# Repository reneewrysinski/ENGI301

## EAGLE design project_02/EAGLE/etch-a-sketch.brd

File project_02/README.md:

This folder contains documentation, EAGLE files, and manufacturing files for my EDES301 PCB design project. This design is a PocketBeagle-based Etch-A-Sketch controlled by two potentiometers and two buttons with a 2.8" TFT screen to display the image being produced.

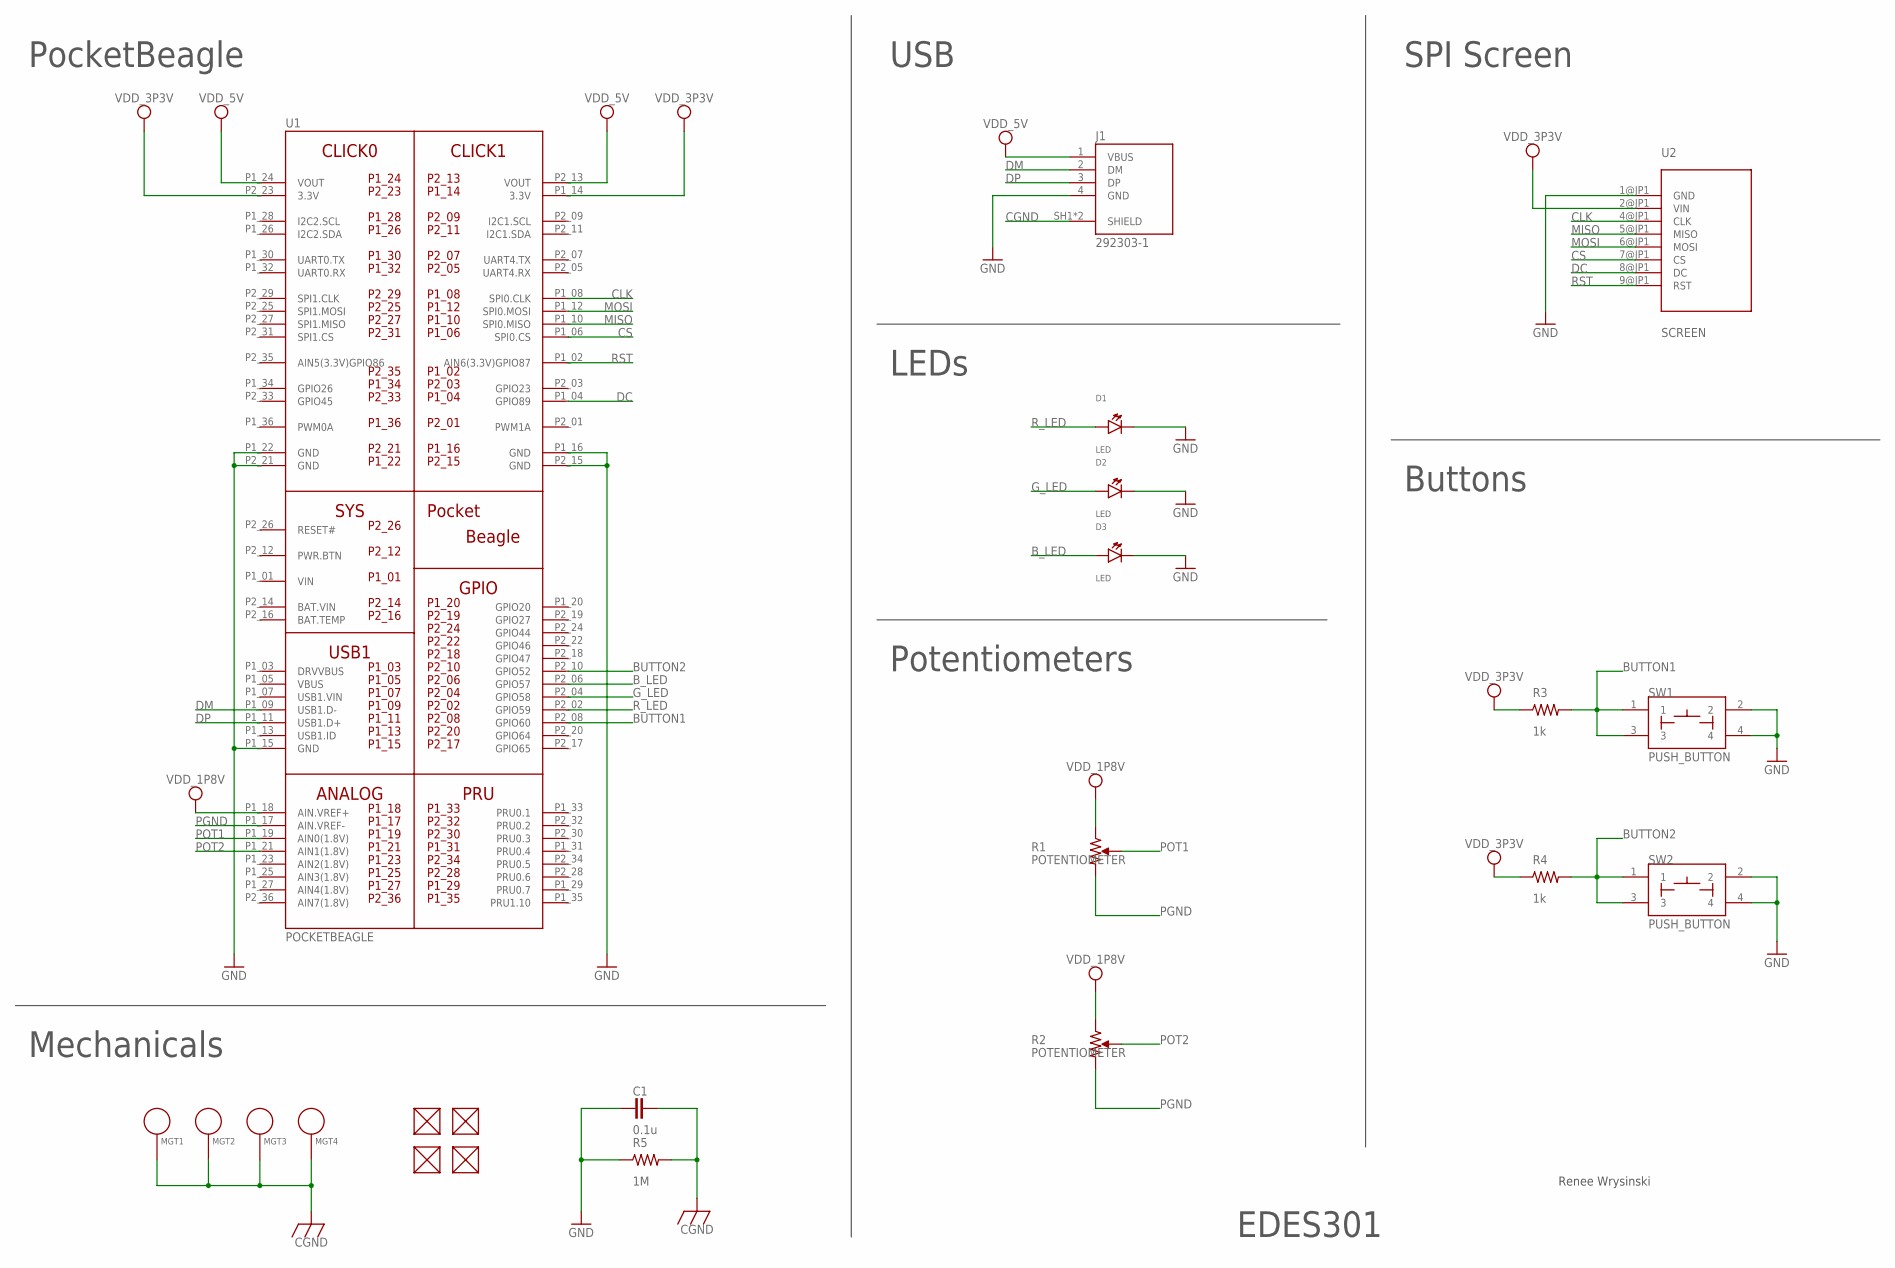
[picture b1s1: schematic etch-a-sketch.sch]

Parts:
C1: 0.1u; C0603
D1, D2, D3: LED; EIA-STD
FUD1, FUD2, FUD3, FUD4: FIDUCIAL; FIDUCIAL_40MIL
J1: 292303-1; TE_292303-1
MGT1, MGT2, MGT3, MGT4: MOUNTING_HOLE
R1, R2: POTENTIOMETER; POT-PO90S
R3, R4: 1k; R0603
R5: 1M; R0603
SW1, SW2: PUSH_BUTTON; BUTTON_12.5MM
U1: POCKETBEAGLE
U2: SCREEN; ADAFRUIT_2.8_TFT_BREAKOUT_V2

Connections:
BAT.VIN: U1.P2_14 (BAT.VIN)
BUTTON1: R3.2, SW1.1, SW1.3, U1.P2_08 (GPIO60)
BUTTON2: R4.2, SW2.1, SW2.3, U1.P2_10 (GPIO52)
B_LED: D3.ANODE, U1.P2_06 (GPIO57)
CGND: C1.2, J1.SH1 (SHIELD), J1.SH2 (SHIELD), MGT1.P$1, MGT2.P$1, MGT3.P$1, MGT4.P$1, R5.2
CLK: U1.P1_08 (SPI0.CLK), U2.4@JP1 (CLK)
CS: U1.P1_06 (SPI0.CS), U2.7@JP1 (CS)
DC: U1.P1_04 (GPIO89), U2.8@JP1 (DC)
DM: J1.2 (DM), U1.P1_09 (USB1.D-)
DP: J1.3 (DP), U1.P1_11 (USB1.D+)
GND: C1.1, D1.CATHODE, D2.CATHODE, D3.CATHODE, J1.4 (GND), R5.1, SW1.2, SW1.4, SW2.2, SW2.4, U1.P1_15 (GND), U1.P1_16 (GND), U1.P1_22 (GND), U1.P2_15 (GND), U1.P2_21 (GND), U2.1@JP1 (GND)
G_LED: D2.ANODE, U1.P2_04 (GPIO58)
MISO: U1.P1_10 (SPI0.MISO), U2.5@JP1 (MISO)
MOSI: U1.P1_12 (SPI0.MOSI), U2.6@JP1 (MOSI)
PGND: R1.CW, R2.CW, U1.P1_17 (AIN.VREF-)
POT1: R1.S, U1.P1_19 (AIN0(1.8V))
POT2: R2.S, U1.P1_21 (AIN1(1.8V))
RST: U1.P1_02 (AIN6(3.3V)GPIO87), U2.9@JP1 (RST)
R_LED: D1.ANODE, U1.P2_02 (GPIO59)
VDD_1P8V: R1.CCW, R2.CCW, U1.P1_18 (AIN.VREF+)
VDD_3P3V: R3.1, R4.1, U1.P1_14 (3.3V), U1.P2_23 (3.3V), U2.2@JP1 (VIN)
VDD_5V: J1.1 (VBUS), U1.P1_24 (VOUT), U1.P2_13 (VOUT)
VIN: U1.P1_01 (VIN)

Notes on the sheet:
PocketBeagle
Mechanicals
USB
LEDs
Potentiometers
Buttons
SPI Screen
EDES301
Renee Wrysinski

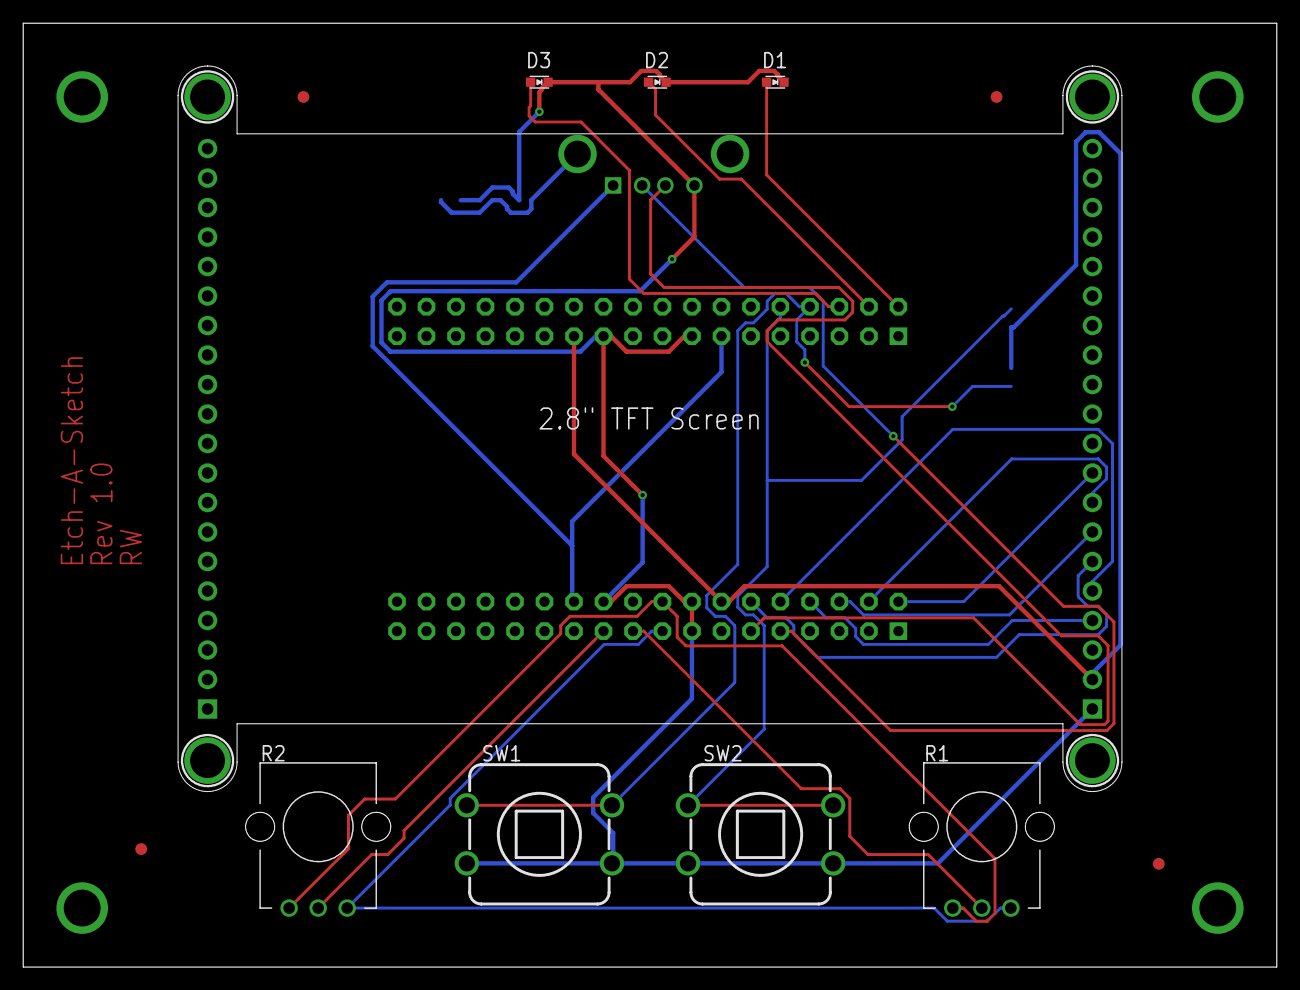
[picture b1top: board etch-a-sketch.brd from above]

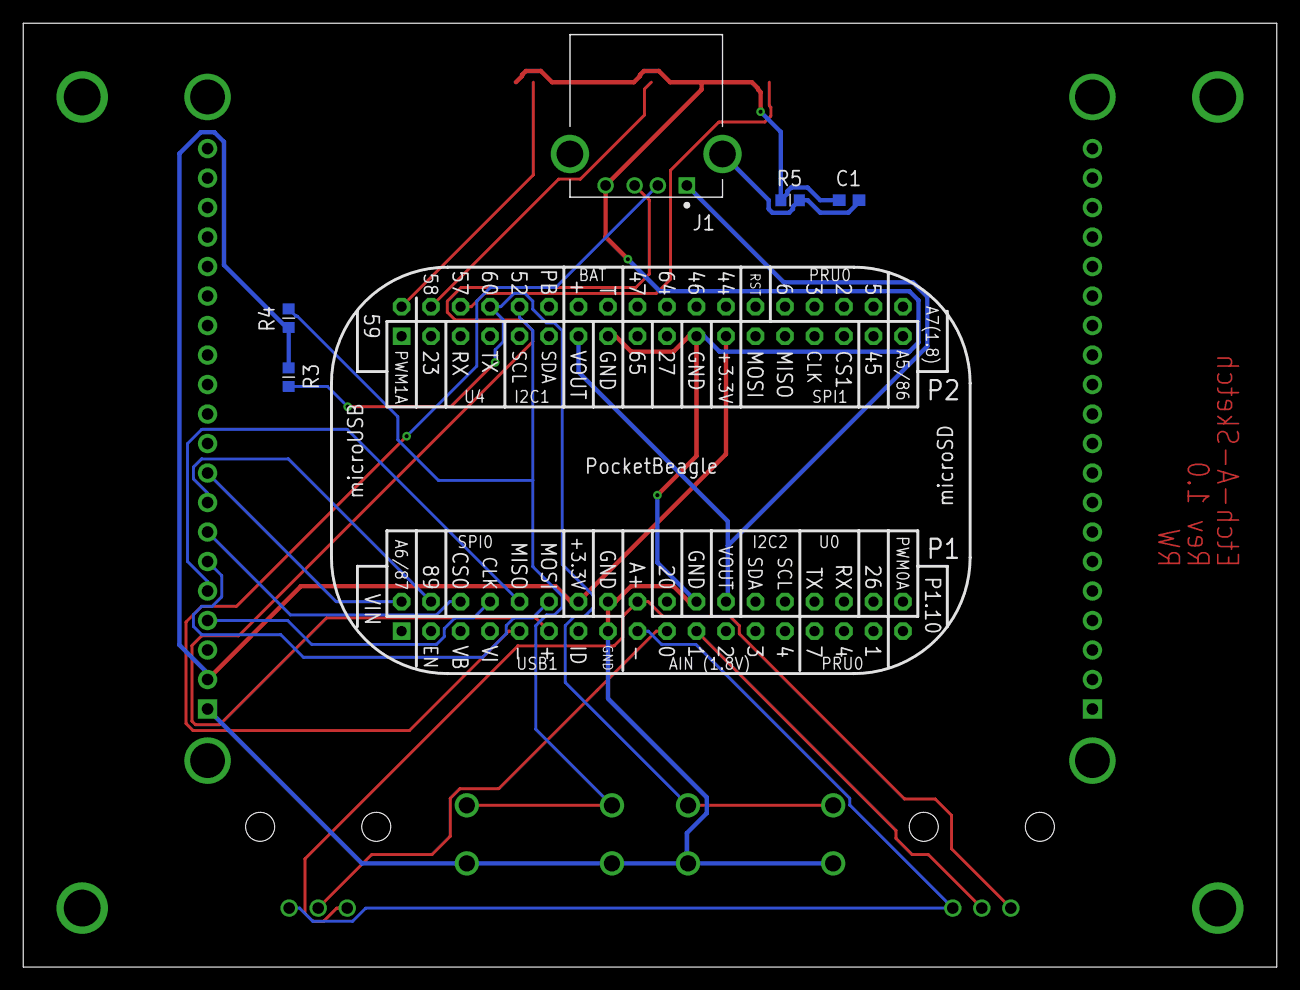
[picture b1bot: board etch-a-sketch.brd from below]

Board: 2 copper layers, 108.0 x 81.3 mm, 22 parts (6 on the bottom side), 21 nets.

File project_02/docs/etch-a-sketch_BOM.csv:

"Qty";"Value";"Device";"Package";"Parts";"Description";"AVAILABILITY";"CENTERLINE_PITCH";"COMMENT";"DESCRIPTION";"EU_ROHS_COMPLIANCE";"MF";"MP";"NUMBER_OF_POSITIONS";"PACKAGE";"PRICE";"PRODUCT_TYPE";"PURCHASE-URL";
"1";"0.1u";"C_C0603";"C0603";"C1";"Capacitor SMD.";"";"";"";"";"";"";"";"";"";"";"";"";
"1";"1M";"R_R0603";"R0603";"R5";"RESISTOR, American symbol";"";"";"";"";"";"";"";"";"";"";"";"";
"2";"1k";"R_R0603";"R0603";"R3, R4";"RESISTOR, American symbol";"";"";"";"";"";"";"";"";"";"";"";"";
"1";"292303-1";"292303-1";"TE_292303-1";"J1";"CONN USB RECEPT R/A TYPE A 4POS Check availability";"In Stock";"2 mm[.078 in]";"292303-1";" Conn";" Data";" USB";" Recept";" 2.0";" 4 Pos";" 1 Port";" Rt Angle";" A Ser";
"4";"FIDUCIAL";"FIDUCIAL";"FIDUCIAL_40MIL";"FUD1, FUD2, FUD3, FUD4";"";"";"";"";"";"";"";"";"";"";"";"";"";
"3";"LED";"LED";"EIA-STD";"D1, D2, D3";"EIA-STD LED, LTST-C191TBKT";"";"";"";"";"";"";"";"";"";"";"";"";
"4";"MOUNTING_HOLE";"MOUNTING_HOLE";"MOUNTING_HOLE";"MGT1, MGT2, MGT3, MGT4";"Chassis Mounting Hole w/GND connection ability";"";"";"";"";"";"";"";"";"";"";"";"";
"1";"POCKETBEAGLE";"POCKETBEAGLE";"POCKETBEAGLE";"U1";"";"";"";"";"";"";"";"";"";"";"";"";"";
"2";"POTENTIOMETER";"POTENTIOMETER";"POT-PO90S";"R1, R2";"Potentiometer - Examples:";"";"";"";"";"";"";"";"";"";"";"";"";
"2";"PUSH_BUTTON";"PUSH_BUTTON";"BUTTON_12.5MM";"SW1, SW2";"";"";"";"";"";"";"";"";"";"";"";"";"";
"1";"SCREEN";"ADAFRUIT_2.8_TFT_BREAKOUT_V2";"ADAFRUIT_2.8_TFT_BREAKOUT_V2";"U2";"";"";"";"";"";"";"";"";"";"";"";"";"";

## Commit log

2024-09-27 add test file for pocketbeagle commit
2024-09-27 remove test file
2024-10-02 add README and proposal
2024-10-10 add assignment 4 code
2025-01-11 add required files for submission
2025-01-11 move project 2 to correct location
2025-01-11 added diagram, moved to docs folder
2025-01-11 add python code and updated proposal
2025-01-11 add block diagrams
2025-01-11 fix readme
